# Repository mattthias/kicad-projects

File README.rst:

==============
Kicad projects
==============

This repository contains Kicad projects.

* led-badge_
* esp8266-badge_

.. _led-badge: ./led-badge/ 
.. _esp8266-badge: ./esp8266-badge/

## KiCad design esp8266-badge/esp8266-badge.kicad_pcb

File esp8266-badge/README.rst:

==================
Hedonism Bot badge
==================

This was my first attempt to create an electronic badge. The Hedonism Bot is a character from Futurama_.

I made a mistake with that OLED display, the pinout on the pcb isn't compatible with the most common SSD1306 OLED display.

.. _Futurama: https://theinfosphere.org/images/cache/4/44/Hedonism_Bot.html

Pictures
--------

.. image:: hedonism_render.png
.. image:: hedonism_pcb.png

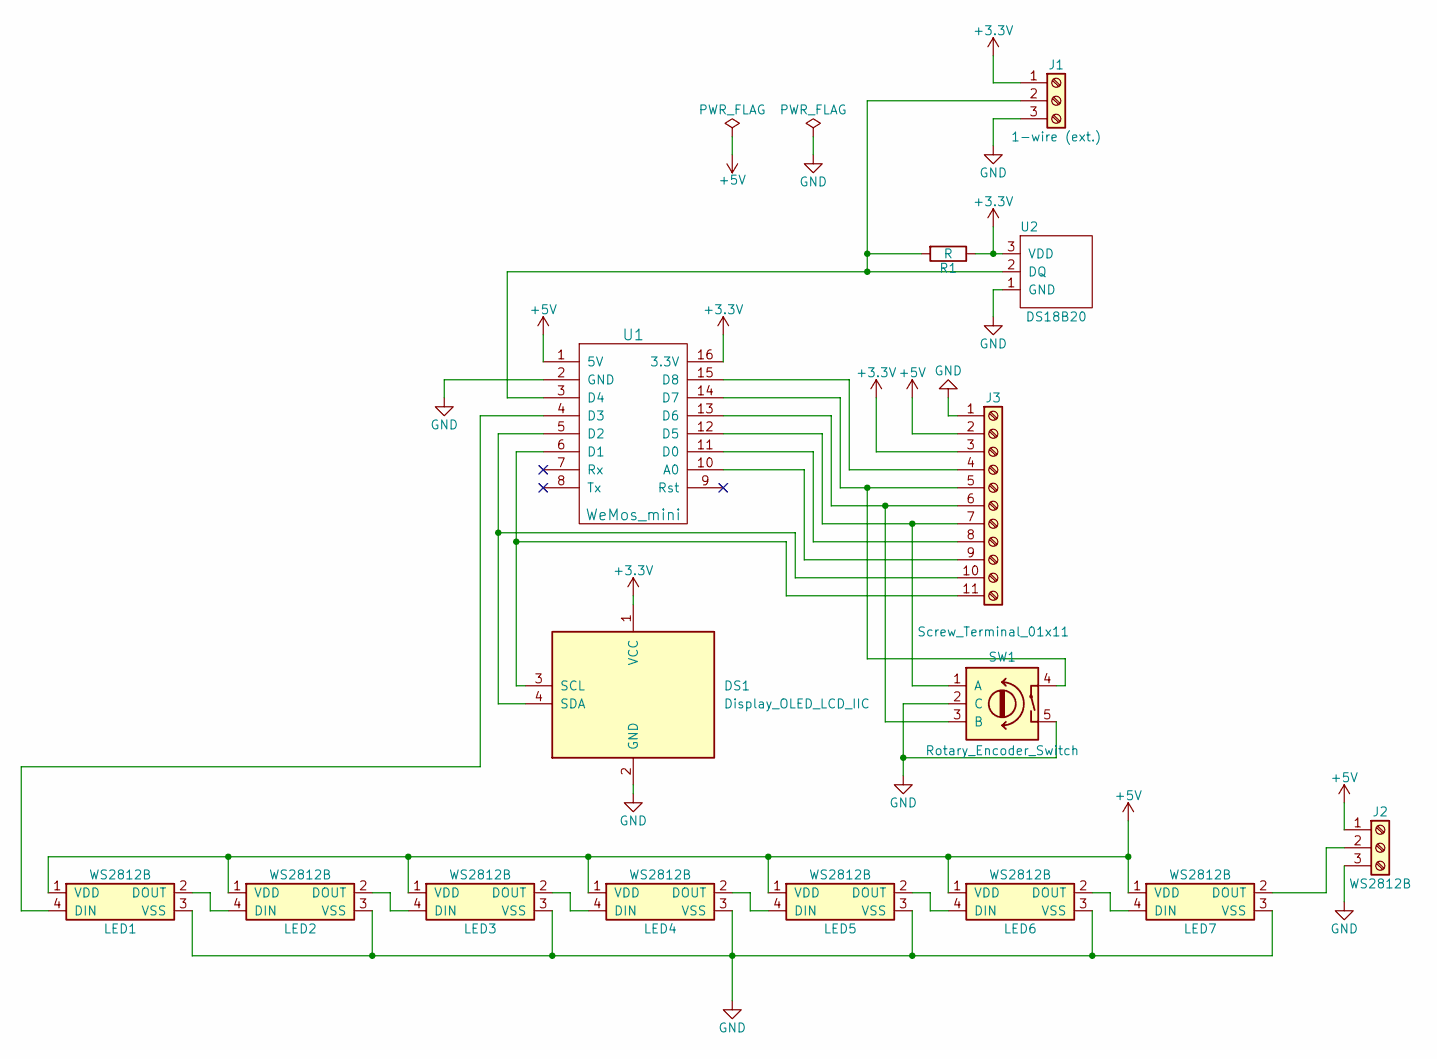
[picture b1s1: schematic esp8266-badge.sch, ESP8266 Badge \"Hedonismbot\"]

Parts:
DS1: Display_OLED_LCD_IIC; LCD_Display_128x64_OLED_Ebay
J1: 1-wire (ext.); Pin_Header_Straight_1x03_Pitch2.54mm
J2: WS2812B; Pin_Header_Straight_1x03_Pitch2.54mm
J3: Screw_Terminal_01x11; Pin_Header_Straight_1x11_Pitch2.54mm
LED1, LED2, LED3, LED4, LED5, LED6, LED7: WS2812B; LED_WS2812B-PLCC4
R1: R; R_Axial_DIN0207_L6.3mm_D2.5mm_P10.16mm_Horizontal
SW1: Rotary_Encoder_Switch; ALPS_STEC12E08_china
U1: WeMos_mini; wemos-d1-mini-with-pin-header-and-connector
U2: DS18B20; TO-92_Inline_Wide

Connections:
+3V3: DS1.1 (VCC), J1.1, J3.3, R1.1, U1.16 (3.3V), U2.3 (VDD); also elsewhere on the board
+5V: J2.1, J3.2, LED1.1 (VDD), LED2.1 (VDD), LED3.1 (VDD), LED4.1 (VDD), LED5.1 (VDD), LED6.1 (VDD), LED7.1 (VDD), U1.1 (5V)
GND: DS1.2 (GND), J1.3, J2.3, J3.1, LED1.3 (VSS), LED2.3 (VSS), LED3.3 (VSS), LED4.3 (VSS), LED5.3 (VSS), LED6.3 (VSS), LED7.3 (VSS), SW1.2 (C), SW1.5, U1.2 (GND), U2.1 (GND); also elsewhere on the board
unnamed: DS1.3 (SCL), J3.11, U1.6 (D1)
unnamed: DS1.4 (SDA), J3.10, U1.5 (D2)
unnamed 5: J1.2, R1.2, U1.3 (D4), U2.2 (DQ); also elsewhere on the board
unnamed: J2.2, LED7.2 (DOUT)
unnamed: J3.4, U1.15 (D8)
unnamed: J3.5, SW1.4, U1.14 (D7)
unnamed: J3.6, SW1.3 (B), U1.13 (D6)
unnamed: J3.7, SW1.1 (A), U1.12 (D5)
unnamed: J3.8, U1.11 (D0)
unnamed: J3.9, U1.10 (A0)
unnamed: LED1.2 (DOUT), LED2.4 (DIN)
unnamed: LED1.4 (DIN), U1.4 (D3)
unnamed: LED2.2 (DOUT), LED3.4 (DIN)
unnamed: LED3.2 (DOUT), LED4.4 (DIN)
unnamed: LED4.2 (DOUT), LED5.4 (DIN)
unnamed: LED5.2 (DOUT), LED6.4 (DIN)
unnamed: LED6.2 (DOUT), LED7.4 (DIN)

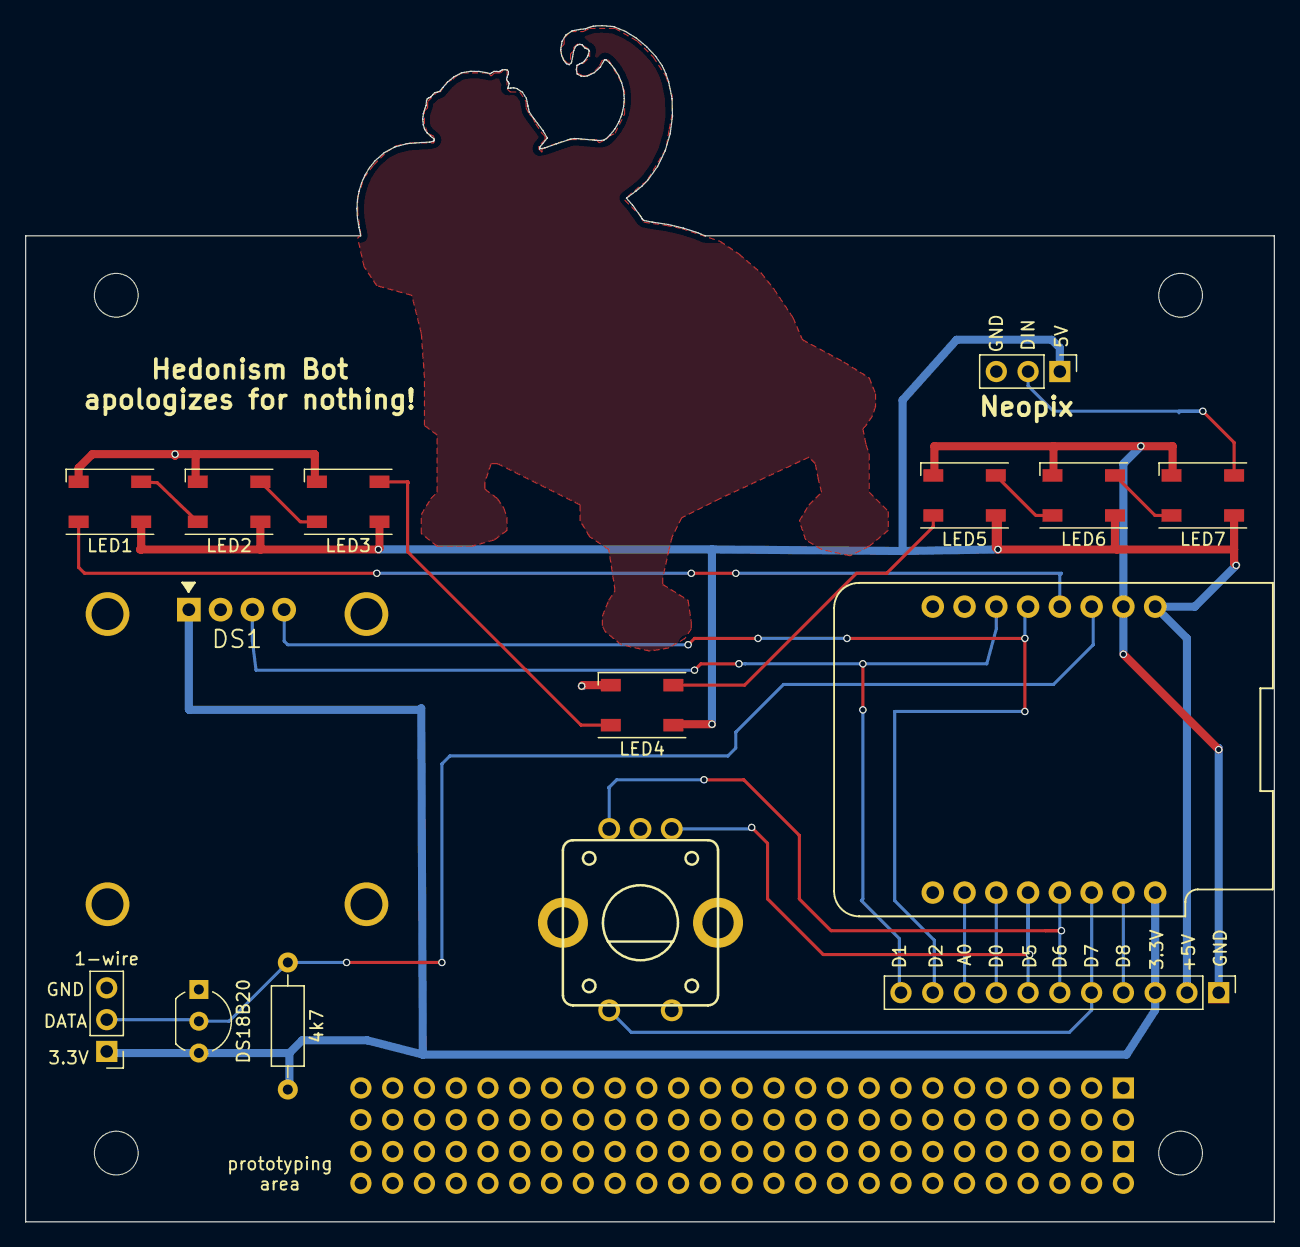
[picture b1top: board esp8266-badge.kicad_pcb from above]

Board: 2 copper layers, 99.8 x 95.6 mm, 15 parts (0 on the bottom side), 20 nets.

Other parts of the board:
DS18B20: DS18B20; TO-92_Inline_Wide

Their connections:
+3V3: DS18B20.3; also elsewhere on the board
GND: DS18B20.1; also elsewhere on the board
unnamed 5: DS18B20.2; also elsewhere on the board

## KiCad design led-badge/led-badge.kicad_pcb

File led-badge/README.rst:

================
Simple LED badge
================

My first Kicad project. The copper layer is "optimized" for laser toner
transfer pcb making (As seen on Instructables_). As the original Kicad footprint
library "Symbols" only had the Kicad logo for the "Silk Screen" layer copied the
footprint to the projects and edited it for use on the copper layer.

Assembly instructions
---------------------

* First solder the resistor. Direction doesnt care.
* Solder the button cell holder fitting the print on the pcb.
* Solder the switch to the pcb. Direction does not care.
* The direction is important for the led. Take a close look: It should have a
  long and a short lead. The shorter lead is the negative lead and should go to
  the square solder pad. If you follow the trace from the square solder pad it
  ends in the middle of the pcb at the negative pin of the button cell holder.

Pictures
--------

.. _Instructables: http://www.instructables.com/id/Cheap-and-Easy-Toner-Transfer-for-PCB-Making/).

.. image:: led-badge_front.png
.. image:: led-badge_bottom.png

The pcbs produced by Smart-Prototyping.com_ . The price was ~10 € for ten pcbs
and shipping to Germany. Took all together (production, shipping, customs) 19 days. 

.. image:: pcbs.png

.. _Smart-Prototyping.com: https://www.smart-prototyping.com

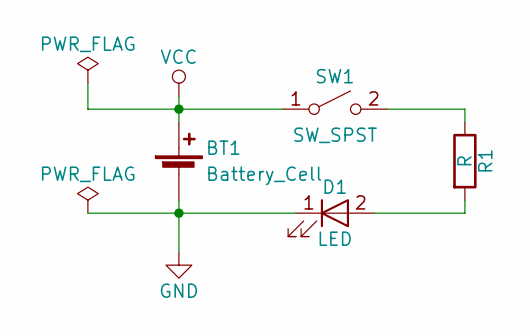
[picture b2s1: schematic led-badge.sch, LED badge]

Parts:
BT1: Battery_Cell; Keystone_105_1x2430-CoinCell
D1: LED; LED_D5.0mm
R1: R; R_Axial_DIN0207_L6.3mm_D2.5mm_P10.16mm_Horizontal
SW1: SW_SPST; Pin_Header_Straight_1x03_Pitch2.54mm

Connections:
GND: BT1.2 (-), D1.1 (K)
unnamed: D1.2 (A), R1.2
unnamed: R1.1, SW1.2 (B)
VCC: BT1.1 (+), SW1.1 (A)

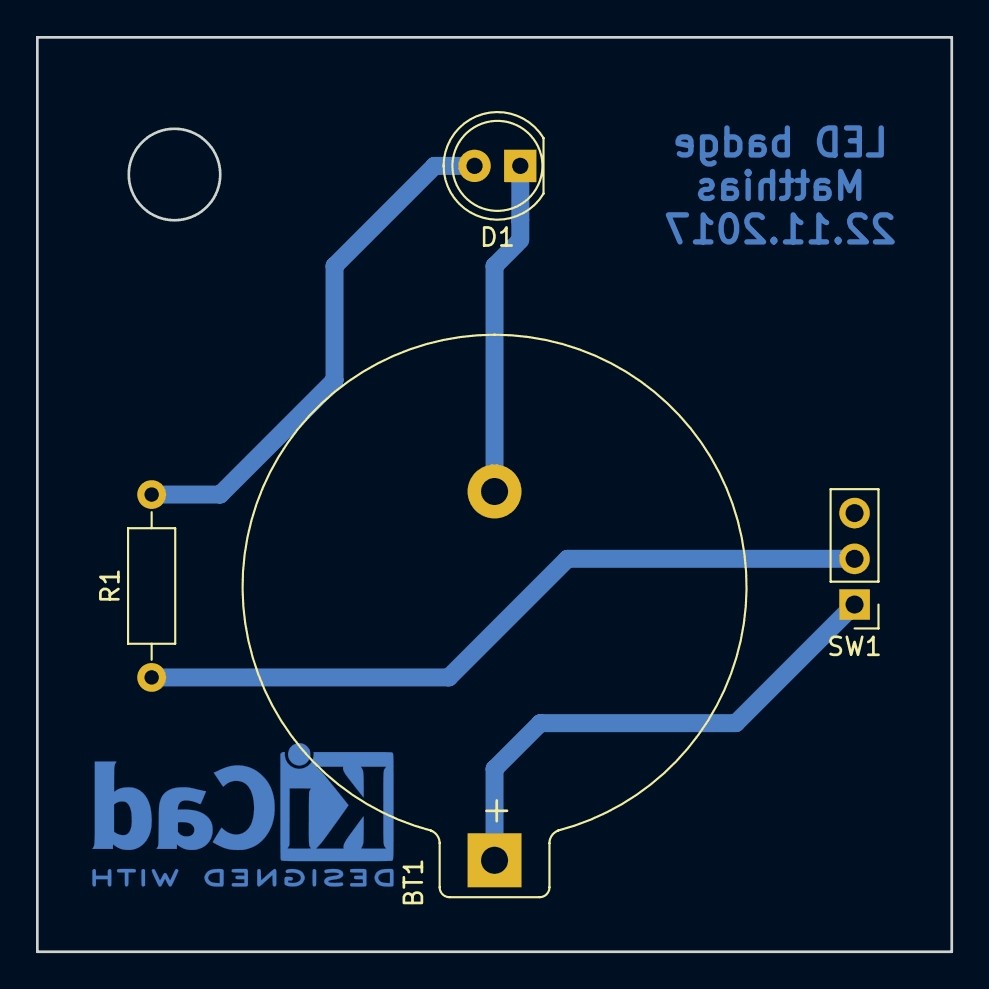
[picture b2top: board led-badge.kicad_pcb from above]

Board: 2 copper layers, 50.8 x 50.8 mm, 5 parts (1 on the bottom side), 4 nets.

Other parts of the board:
kicadlogo: KiCad-Logo2_8mm_SilkScreen

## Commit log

2017-11-27 Add initial version of led-badge
    * gerber/ contains a zip with the used files for production
2017-11-27 Add docs
2017-11-27 Add repository README
2017-12-13 Add photo of the led badge pcb
2017-12-31 Add wemos-d1-mini lib as submodule
2018-01-01 Add lib for 128x64 oled i²c display
2018-01-01 Update submodule wemos-d1-mini-kicad
    * With fixed paths for my project layout 3d models are working now
2018-02-02 Add footprint lib Rotary-Encoders as submodule
2018-02-02 Add "lochraster" footprint in matthias lib
2018-02-02 Add esp8266-badge "hedonismbot"
2026-02-01 Add README
2026-02-01 Update README.rst
    Add link to esp8266 badge
